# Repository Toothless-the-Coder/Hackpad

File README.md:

This project is a custom 11-key mechanical macropad built using the Seeeduino XIAO RP2040 microcontroller and Cherry MX switches. The device primarily functions as a numpad, but it can also transform into a programmable macropad when certain keys are held.
By holding the 0 and 1 keys the device switches software profiles and changes what the keys do from a regular numpad to a macropad.
To use the macropad, simply plug it into your computer using a USB-C cable. The device will automatically be recognized as a keyboard.
In its default mode, the keys act as a numeric keypad. Holding the 0 and 1 keys at the same time activates the macro profile, allowing the keys to trigger custom macros depending on the firmware configuration.
I created this project to design a compact keypad that could serve both as a numpad and a programmable macro controller. Many keyboards (such as mine) do not include a numpad, and having an additional macro layer makes repetitive computer tasks faster and more convenient.
This project was also a way to learn PCB design, CAD modeling, and firmware development for custom hardware.
This design was reviewed and sanity-checked with peers to verify component placement and wiring before fabrication.

| Item | Quantity | Description | Footprint | Link |
|-----|-----|-----|-----|-----|
| Seeed XIAO RP2040 | 1 | Microcontroller | XIAO-RP2040 | https://www.seeedstudio.com/XIAO-RP2040-p-5026.html |
| Cherry MX Switch | 11 | Mechanical key switch | MX | https://www.cherrymx.de/en/cherry-mx.html |
| 1N4148 Diode | 11 | Signal diode | DO-35 / SMD | https://www.vishay.com/docs/81857/1n4148.pdf |
| Kailh Hot Swap Socket | 11 | Switch socket | Kailh MX Socket | https://splitkb.com/products/kailh-hotswap-sockets |
| Keycaps | 11 | MX compatible keycaps | MX | https://kbdfans.com |
| PCB | 1 | Custom Hackpad PCB | Custom | — |
| Case | 1 | 3D printed case | Custom | — |
| Screws | 4 | Case mounting screws | M2 | https://www.mcmaster.com |

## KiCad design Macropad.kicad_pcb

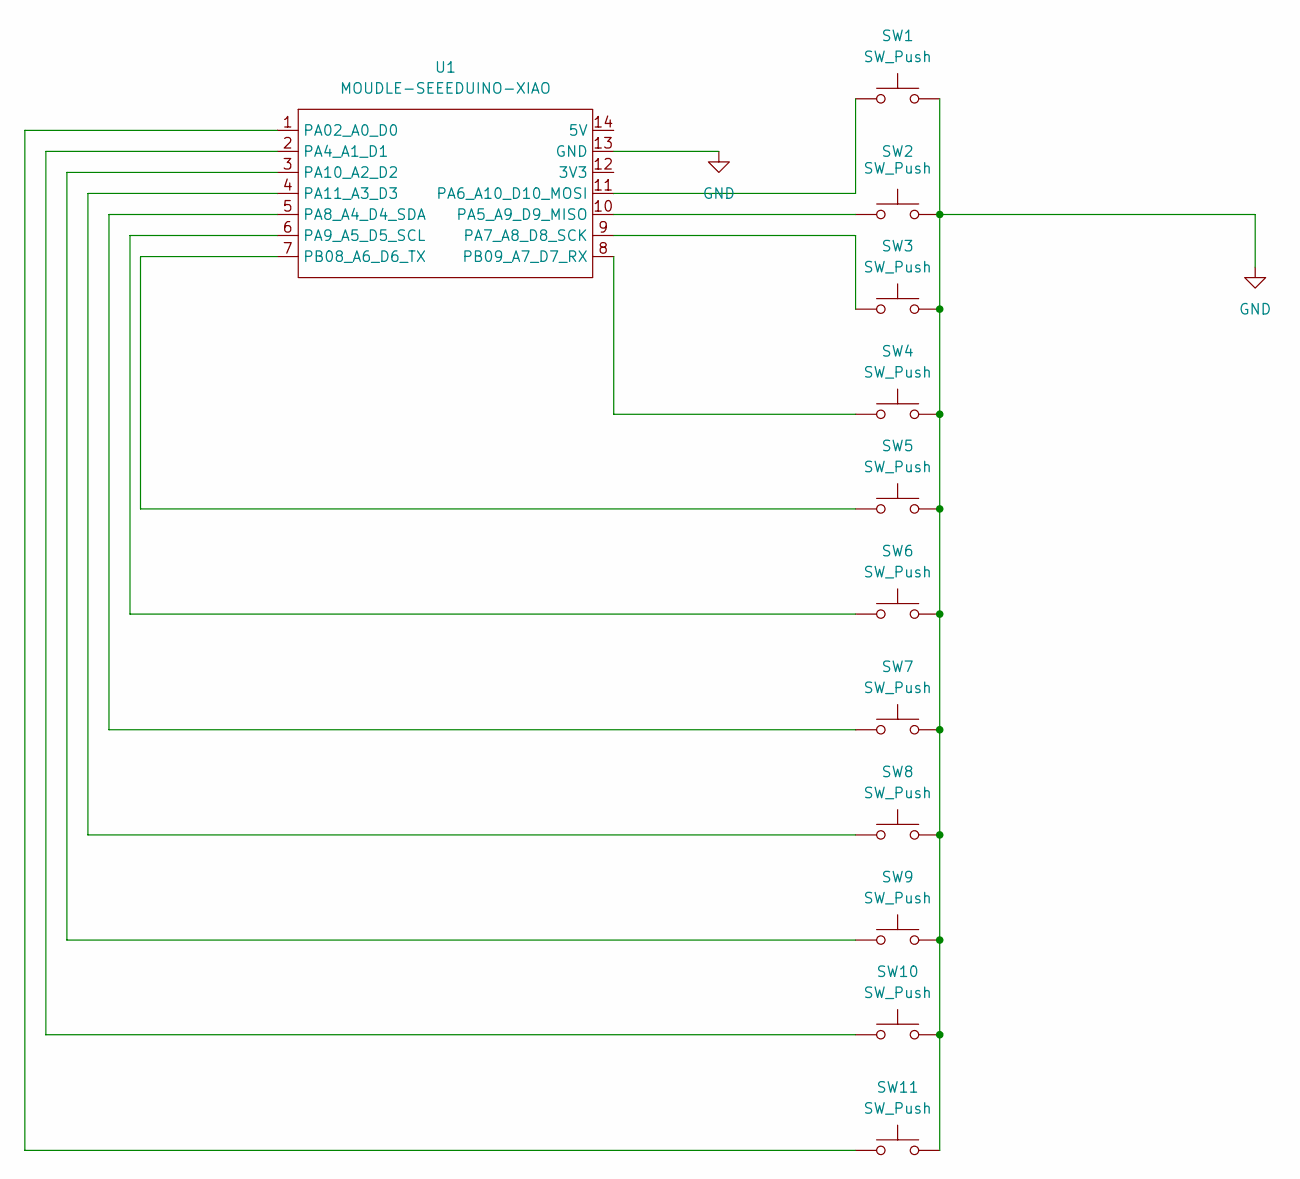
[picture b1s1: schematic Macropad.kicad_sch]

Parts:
SW1, SW2, SW3, SW4, SW5, SW6, SW7, SW8, SW9, SW10, SW11: SW_Push; SW_Cherry_MX_1.00u_PCB
U1: MOUDLE-SEEEDUINO-XIAO; XIAO-Generic-Hybrid-14P-2.54-21X17.8MM

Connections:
GND: SW1.2, SW2.2, SW3.2, SW4.2, SW5.2, SW6.2, SW7.2, SW8.2, SW9.2, SW10.2, SW11.2, U1.13 (GND)
unnamed: SW11.1, U1.1 (PA02_A0_D0)
unnamed: SW10.1, U1.2 (PA4_A1_D1)
unnamed: SW2.1, U1.10 (PA5_A9_D9_MISO)
unnamed: SW1.1, U1.11 (PA6_A10_D10_MOSI)
unnamed: SW3.1, U1.9 (PA7_A8_D8_SCK)
unnamed: SW7.1, U1.5 (PA8_A4_D4_SDA)
unnamed: SW6.1, U1.6 (PA9_A5_D5_SCL)
unnamed: SW9.1, U1.3 (PA10_A2_D2)
unnamed: SW8.1, U1.4 (PA11_A3_D3)
unnamed: SW5.1, U1.7 (PB08_A6_D6_TX)
unnamed: SW4.1, U1.8 (PB09_A7_D7_RX)

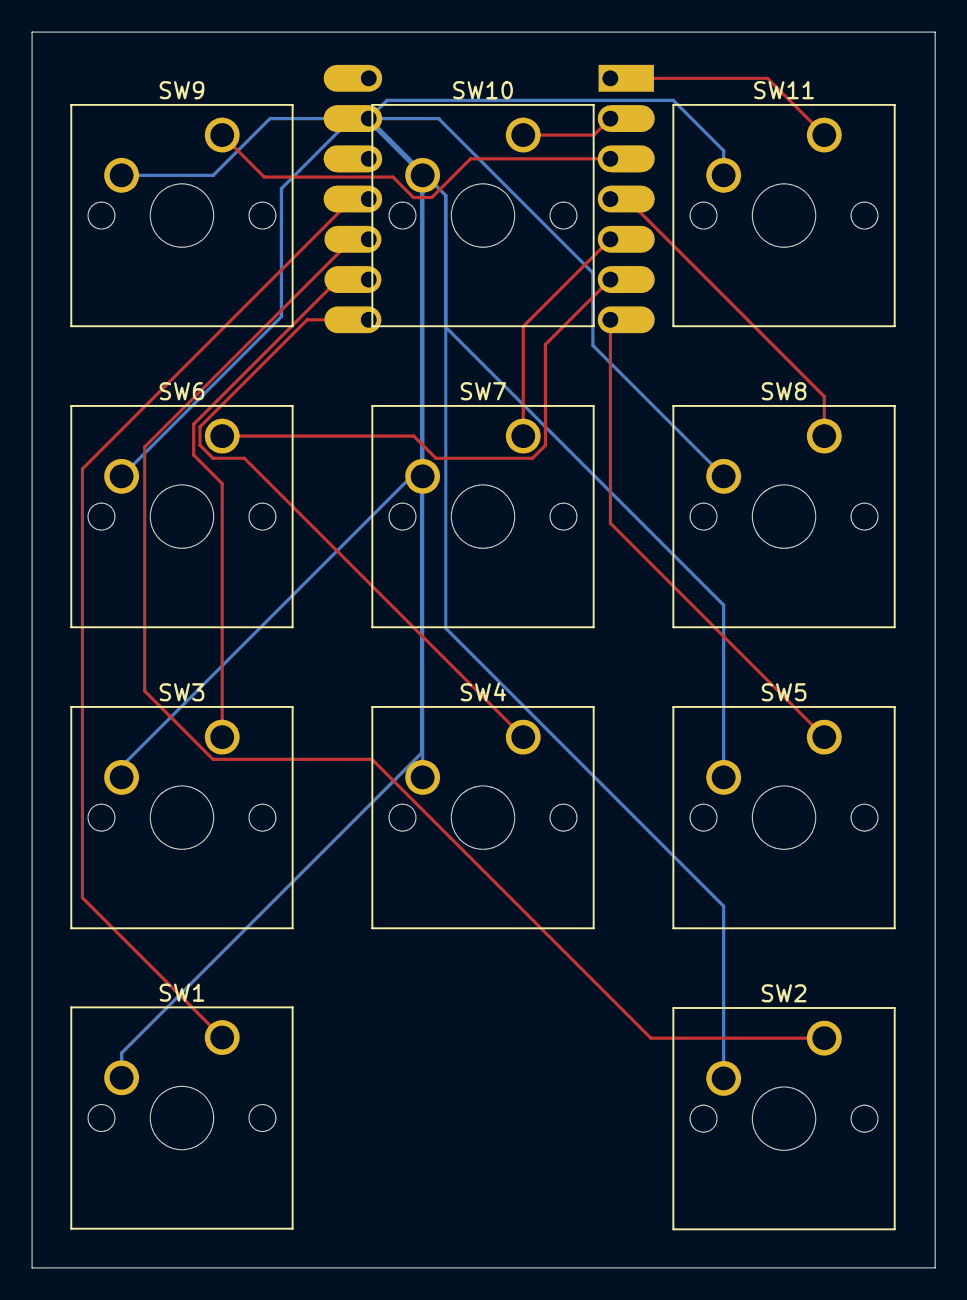
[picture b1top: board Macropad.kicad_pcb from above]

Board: 2 copper layers, 57.0 x 78.0 mm, 12 parts (1 on the bottom side), 12 nets.

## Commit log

2026-03-13 Add files via upload
    These are the schematics and pcb files for my hackpad
2026-03-13 Add files via upload
    This is the 3d model of the case
